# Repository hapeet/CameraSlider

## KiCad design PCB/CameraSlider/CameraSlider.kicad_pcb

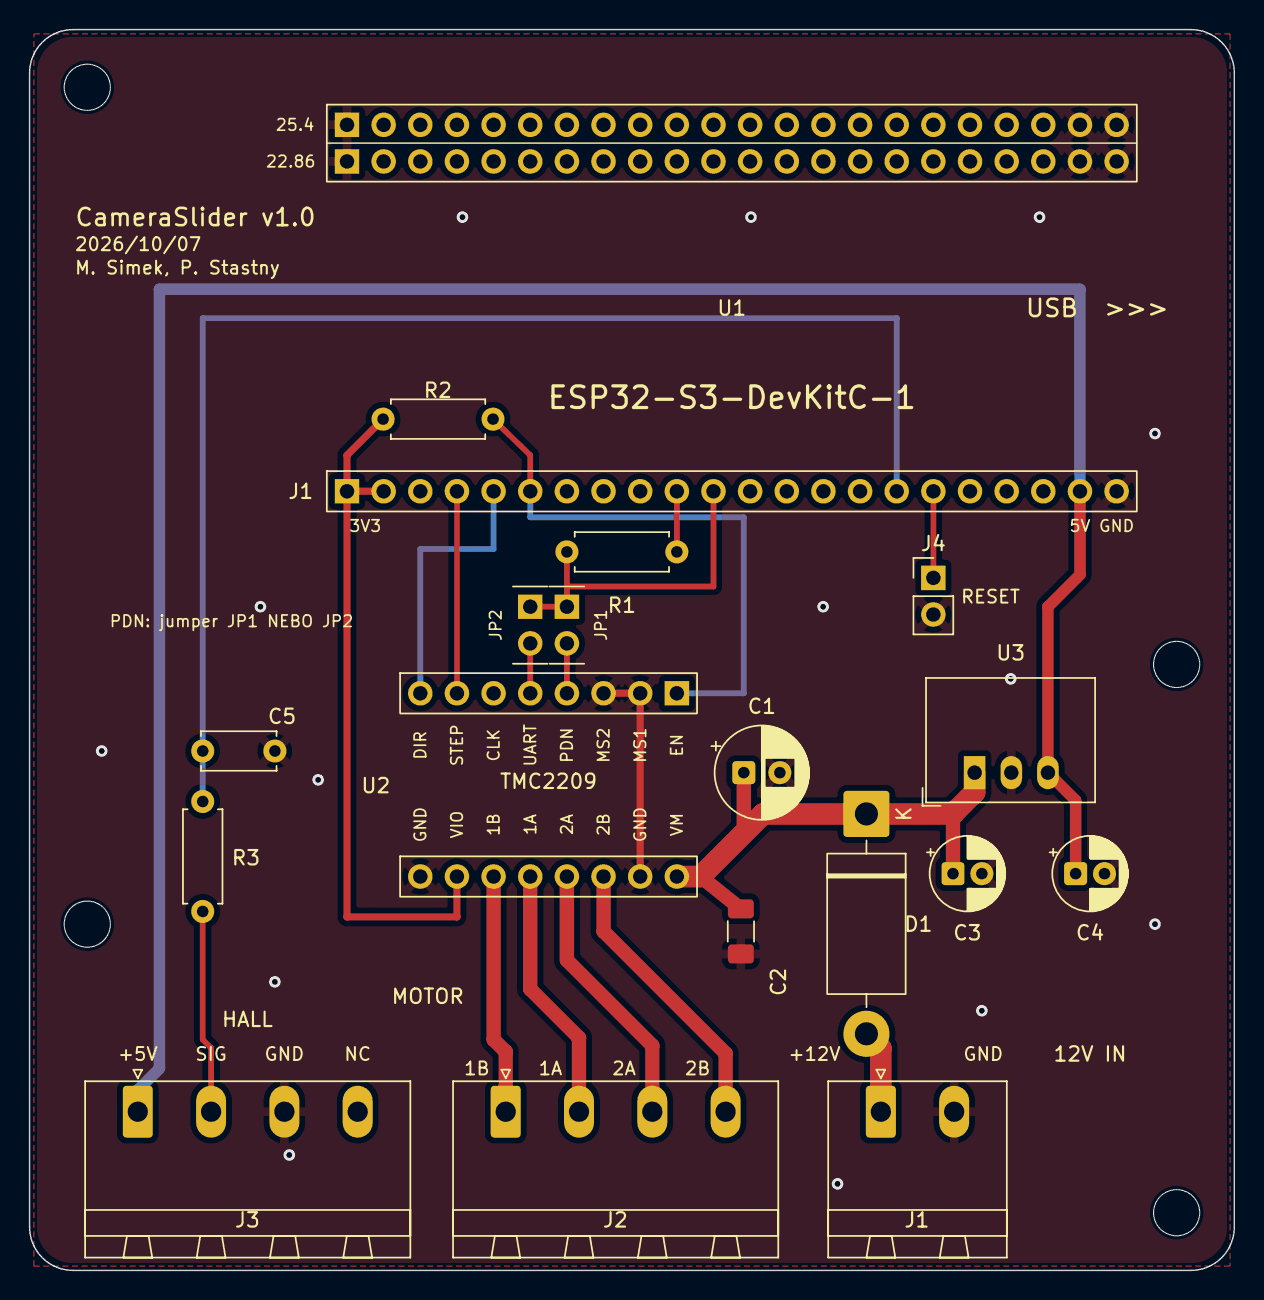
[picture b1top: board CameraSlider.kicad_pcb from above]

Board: 2 copper layers, 83.5 x 86.0 mm, 22 parts (0 on the bottom side), 19 nets.

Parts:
C1: 100uF 35V; CP_Radial_D6.3mm_P2.50mm
C2: 100nF 50V; C_1206_3216Metric_Pad1.33x1.80mm_HandSolder
C3: 10uF 25V; CP_Radial_D5.0mm_P2.00mm
C4: 22uF 10V; CP_Radial_D5.0mm_P2.00mm
C5: 1nF; C_Disc_D5.0mm_W2.5mm_P5.00mm
D1: 1N5822; D_DO-201AD_P15.24mm_Horizontal
H1, H2, H3, H4: M3; MountingHole_3.2mm_M3
J1: 12V IN (Weidmuller SL 5.08/2/90); PhoenixContact_MSTBA_2,5_2-G-5,08_1x02_P5.08mm_Horizontal
J2: MOTOR (Weidmuller SL 5.08/4/90); PhoenixContact_MSTBA_2,5_4-G-5,08_1x04_P5.08mm_Horizontal
J3: HALL (Weidmuller SL 5.08/4/90); PhoenixContact_MSTBA_2,5_4-G-5,08_1x04_P5.08mm_Horizontal
J4: RESET jumper; PinHeader_1x02_P2.54mm_Vertical
JP1: PDN pin4; PinHeader_1x02_P2.54mm_Jumper
JP2: PDN pin5; PinHeader_1x02_P2.54mm_Jumper
R1, R3: 1k; R_Axial_DIN0207_L6.3mm_D2.5mm_P7.62mm_Horizontal
R2: 10k; R_Axial_DIN0207_L6.3mm_D2.5mm_P7.62mm_Horizontal
U1: ESP32-S3-DevKitC-1 N16R8; ESP32-S3-DevKitC-1_Socket
U2: TMC2209 StepperDriver; TMC2209_StepStick_Socket
U3: R-78E5.0-1.0 / K7805-1000R3; Converter_DCDC_RECOM_R-78E-0.5_THT

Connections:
+3V3: R2.1, U1.1, U1.2, U2.10
+5V: C4.1, J3.1, U1.21, U3.3 (VOUT)
+12V: C1.1, C2.1, C3.1, D1.1, U2.16, U3.1 (VIN)
/DIR: U1.5, U2.8
/EN: R2.2, U1.6, U2.1
/ESP_TX: R1.2, U1.10
/HALL: C5.1, R3.1, U1.16
/HALL_EXT: J3.2, R3.2
/MOT_1A: J2.2, U2.12
/MOT_1B: J2.1, U2.11
/MOT_2A: J2.3, U2.13
/MOT_2B: J2.4, U2.14
/PDN4: JP1.2, U2.4
/PDN5: JP2.2, U2.5
/RST_JMP: J4.1, U1.17
/STEP: U1.4, U2.7
/TMC_UART / ESP_RX: JP1.1, JP2.1, R1.1, U1.11
GND: C1.2, C2.2, C3.2, C4.2, C5.2, J1.2, J3.3, J4.2, U1.22, U1.23, U1.43, U1.44, U2.2, U2.3, U2.9, U2.15, U3.2 (GND)
VIN: D1.2, J1.1
